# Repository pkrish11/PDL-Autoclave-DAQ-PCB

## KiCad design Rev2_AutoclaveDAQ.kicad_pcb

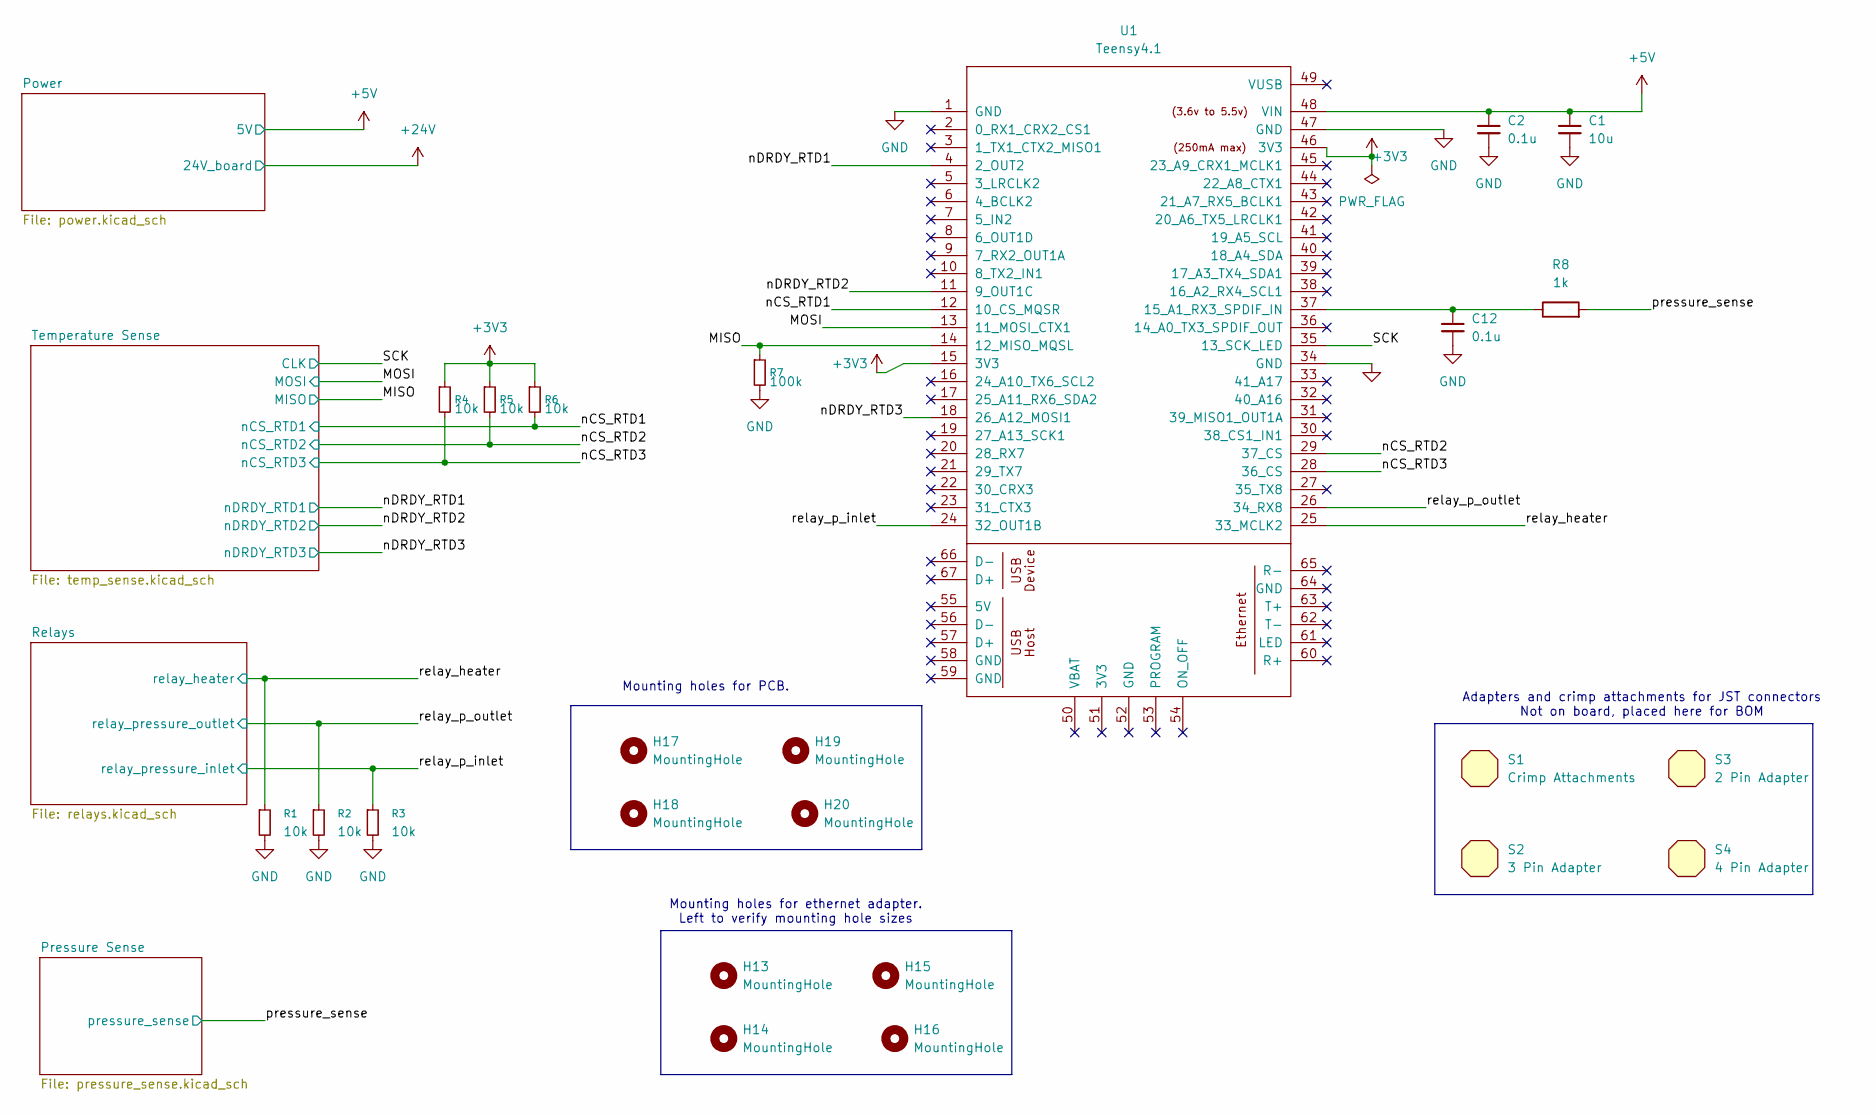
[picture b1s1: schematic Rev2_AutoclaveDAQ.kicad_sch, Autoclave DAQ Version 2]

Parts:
C1: 10u; C_0805_2012Metric; DigiKey_Part_Number 1276-2872-1-ND
C2, C12: 0.1u; C_0805_2012Metric; DigiKey_Part_Number 399-C0805C104K5RACTUCT-ND
H13, H14, H15, H16, H17, H18, H19, H20: MountingHole; MountingHole_3.2mm_M3
R1, R2, R3, R4, R5, R6: 10k; R_0805_2012Metric; DigiKey_Part_Number RMCF0805FT10K0CT-ND
R7: 100k; R_0805_2012Metric; DigiKey_Part_Number P100KDACT-ND
R8: 1k; R_0805_2012Metric; DigiKey_Part_Number 541-1.00KCCT-ND
S1: Crimp Attachments; DigiKey_Part_Number 455-1135TR-ND
S2: 3 Pin Adapter; DigiKey_Part_Number 455-2219-ND
S3: 2 Pin Adapter; DigiKey_Part_Number 455-2266-ND
S4: 4 Pin Adapter; DigiKey_Part_Number 455-2267-ND
U1: Teensy4.1; Teensy41

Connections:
+3V3: R4.1, R5.1, R6.1, U1.15 (3V3), U1.46 (3V3); also elsewhere on the board
+5V: C1.1, C2.1, U1.48 (VIN); also elsewhere on the board
/MISO: R7.1, U1.14 (12_MISO_MQSL); also elsewhere on the board
/MOSI: U1.13 (11_MOSI_CTX1); also elsewhere on the board
/SCK: U1.35 (13_SCK_LED); also elsewhere on the board
/nCS_RTD1: R6.2, U1.12 (10_CS_MQSR); also elsewhere on the board
/nCS_RTD2: R5.2, U1.29 (37_CS); also elsewhere on the board
/nCS_RTD3: R4.2, U1.28 (36_CS); also elsewhere on the board
/nDRDY_RTD1: U1.4 (2_OUT2); also elsewhere on the board
/nDRDY_RTD2: U1.11 (9_OUT1C); also elsewhere on the board
/nDRDY_RTD3: U1.18 (26_A12_MOSI1); also elsewhere on the board
/pressure_sense: R8.2; also elsewhere on the board
/relay_heater: R1.1, U1.25 (33_MCLK2); also elsewhere on the board
/relay_p_inlet: R3.1, U1.24 (32_OUT1B); also elsewhere on the board
/relay_p_outlet: R2.1, U1.26 (34_RX8); also elsewhere on the board
GND: C1.2, C2.2, C12.2, R1.2, R2.2, R3.2, R7.2, U1.1 (GND), U1.34 (GND), U1.47 (GND); also elsewhere on the board
unnamed: C12.1, R8.1, U1.37 (15_A1_RX3_SPDIF_IN)

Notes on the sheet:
Adapters and crimp attachments for JST connectors Not on board, placed here for BOM
Mounting holes for ethernet adapter. Left to verify mounting hole sizes
Mounting holes for PCB.

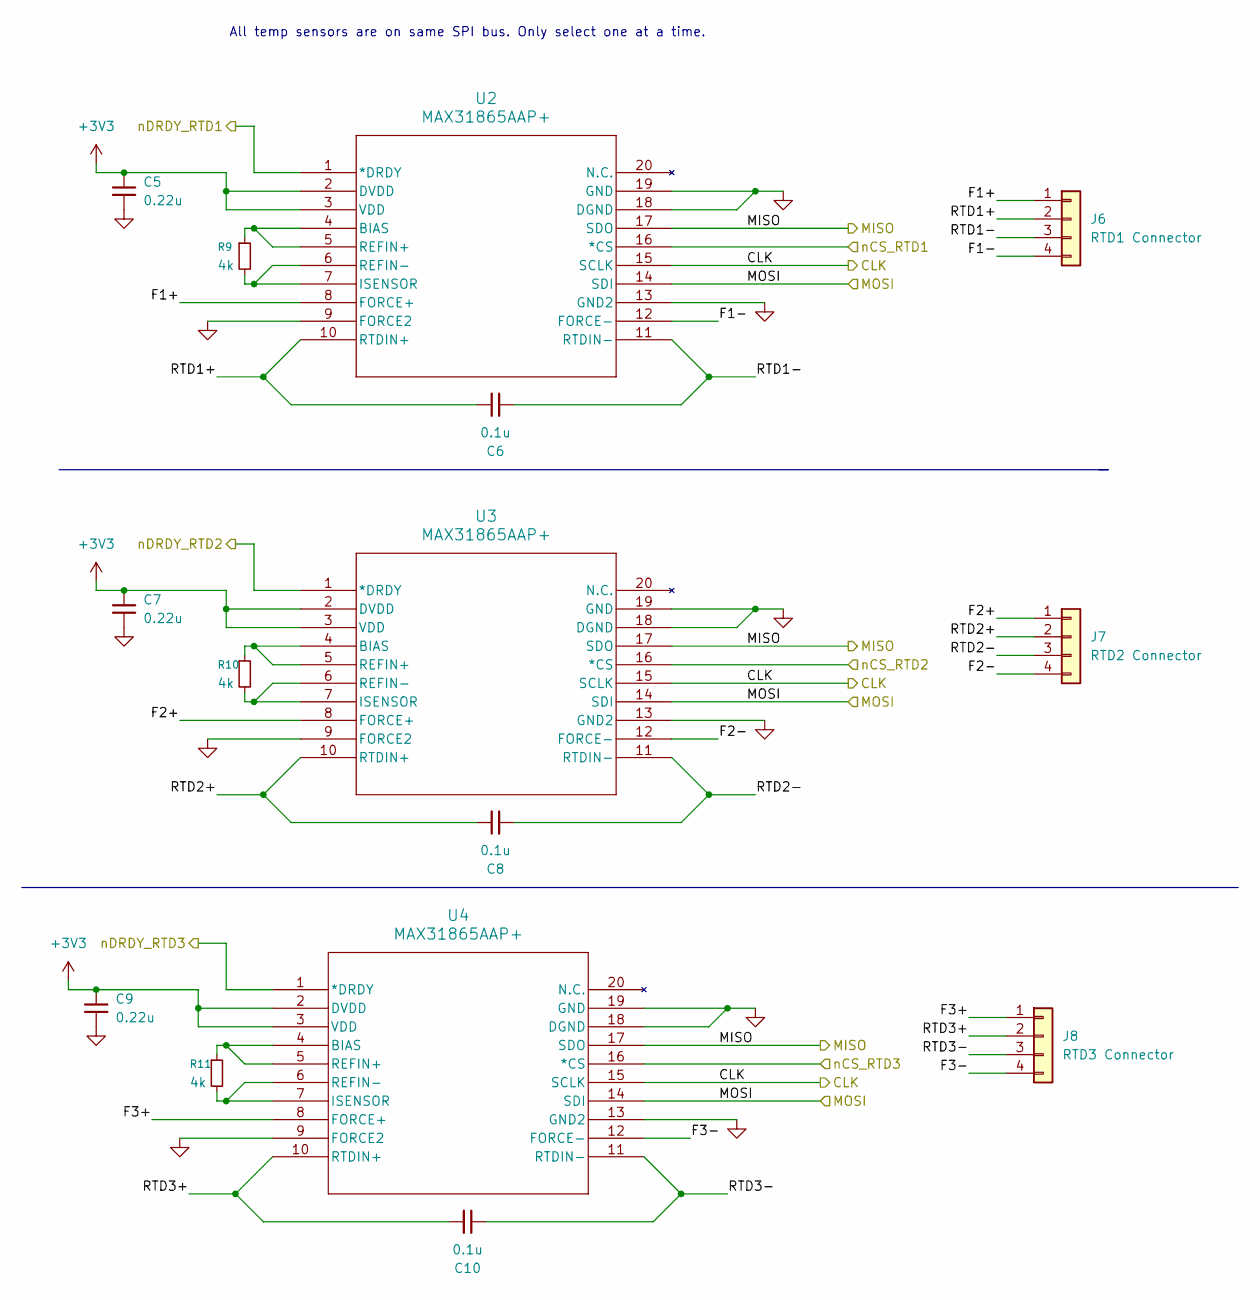
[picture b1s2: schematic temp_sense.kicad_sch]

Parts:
C5, C7, C9: 0.22u; C_0805_2012Metric; DigiKey_Part_Number 399-C0805C224K5RACTUCT-ND
C6, C8, C10: 0.1u; C_0805_2012Metric; DigiKey_Part_Number 399-C0805C104K5RACTUCT-ND
J6: RTD1 Connector; JST_XH_B4B-XH-A_1x04_P2.50mm_Vertical; DigiKey_Part_Number 455-B4B-XH-A-ND
J7: RTD2 Connector; JST_XH_B4B-XH-A_1x04_P2.50mm_Vertical; DigiKey_Part_Number 455-B4B-XH-A-ND
J8: RTD3 Connector; JST_XH_B4B-XH-A_1x04_P2.50mm_Vertical; DigiKey_Part_Number 455-B4B-XH-A-ND
R9, R10, R11: 4k; R_0805_2012Metric; DigiKey_Part_Number 738-RNCF0805BTY4K00CT-ND
U2, U3, U4: MAX31865AAP+; 21-0056C_20_MXM-M; DigiKey_Part_Number MAX31865AAP+

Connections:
+3V3: C5.1, C7.1, C9.1, U2.2 (DVDD), U2.3 (VDD), U3.2 (DVDD), U3.3 (VDD), U4.2 (DVDD), U4.3 (VDD); also elsewhere on the board
/MISO: U2.17 (SDO), U3.17 (SDO), U4.17 (SDO); also elsewhere on the board
/MOSI: U2.14 (SDI), U3.14 (SDI), U4.14 (SDI); also elsewhere on the board
/SCK: U2.15 (SCLK), U3.15 (SCLK), U4.15 (SCLK); also elsewhere on the board
/Temperature Sense/F1+: J6.1, U2.8 (FORCE+)
/Temperature Sense/F1-: J6.4, U2.12 (FORCE-)
/Temperature Sense/F2+: J7.1, U3.8 (FORCE+)
/Temperature Sense/F2-: J7.4, U3.12 (FORCE-)
/Temperature Sense/F3+: J8.1, U4.8 (FORCE+)
/Temperature Sense/F3-: J8.4, U4.12 (FORCE-)
/Temperature Sense/RTD1+: C6.1, J6.2, U2.10 (RTDIN+)
/Temperature Sense/RTD1-: C6.2, J6.3, U2.11 (RTDIN-)
/Temperature Sense/RTD2+: C8.1, J7.2, U3.10 (RTDIN+)
/Temperature Sense/RTD2-: C8.2, J7.3, U3.11 (RTDIN-)
/Temperature Sense/RTD3+: C10.1, J8.2, U4.10 (RTDIN+)
/Temperature Sense/RTD3-: C10.2, J8.3, U4.11 (RTDIN-)
/nCS_RTD1: U2.16 (*CS); also elsewhere on the board
/nCS_RTD2: U3.16 (*CS); also elsewhere on the board
/nCS_RTD3: U4.16 (*CS); also elsewhere on the board
/nDRDY_RTD1: U2.1 (*DRDY); also elsewhere on the board
/nDRDY_RTD2: U3.1 (*DRDY); also elsewhere on the board
/nDRDY_RTD3: U4.1 (*DRDY); also elsewhere on the board
GND: C5.2, C7.2, C9.2, U2.9 (FORCE2), U2.13 (GND2), U2.18 (DGND), U2.19 (GND), U3.9 (FORCE2), U3.13 (GND2), U3.18 (DGND), U3.19 (GND), U4.9 (FORCE2), U4.13 (GND2), U4.18 (DGND), U4.19 (GND); also elsewhere on the board
unnamed: R9.1, U2.4 (BIAS), U2.5 (REFIN+)
unnamed: R9.2, U2.6 (REFIN-), U2.7 (ISENSOR)
unnamed: R10.1, U3.4 (BIAS), U3.5 (REFIN+)
unnamed: R10.2, U3.6 (REFIN-), U3.7 (ISENSOR)
unnamed: R11.1, U4.4 (BIAS), U4.5 (REFIN+)
unnamed: R11.2, U4.6 (REFIN-), U4.7 (ISENSOR)

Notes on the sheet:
All temp sensors are on same SPI bus. Only select one at a time.

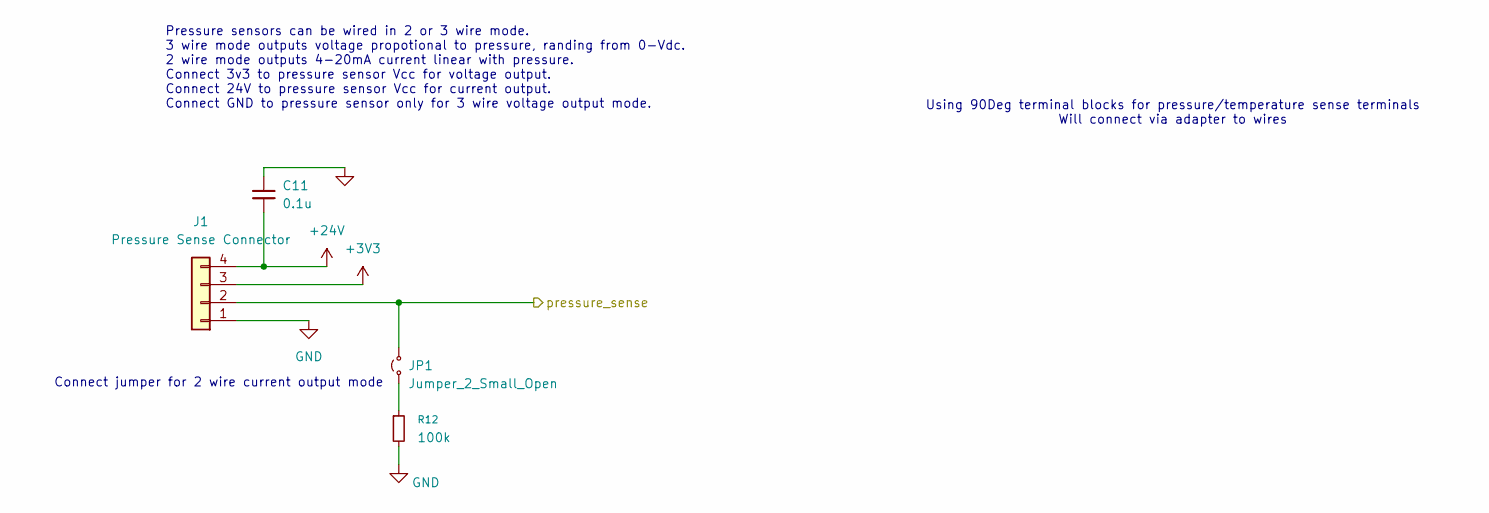
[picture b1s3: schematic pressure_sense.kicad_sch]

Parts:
C11: 0.1u; C_0805_2012Metric; DigiKey_Part_Number 399-C0805C104K5RACTUCT-ND
J1: Pressure Sense Connector; JST_XH_B4B-XH-A_1x04_P2.50mm_Vertical; DigiKey_Part_Number 455-B4B-XH-A-ND
JP1: Jumper_2_Small_Open; PinHeader_1x02_P2.54mm_Vertical
R12: 100k; R_0805_2012Metric; DigiKey_Part_Number P100KDACT-ND

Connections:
+3V3: J1.3; also elsewhere on the board
+24V: C11.2, J1.4; also elsewhere on the board
/pressure_sense: J1.2, JP1.2 (B); also elsewhere on the board
GND: C11.1, J1.1, R12.2; also elsewhere on the board
unnamed: JP1.1 (A), R12.1

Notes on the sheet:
Connect jumper for 2 wire current output mode
Using 90Deg terminal blocks for pressure/temperature sense terminals Will connect via adapter to wires
Pressure sensors can be wired in 2 or 3 wire mode. 3 wire mode outputs voltage propotional to pressure, randing from 0-Vdc. 2 wire mode outputs 4-20mA current linear with pressure. Connect 3v3 to pressure sensor Vcc for voltage output. Connect 24V to pressure sensor Vcc for current output. Connect 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

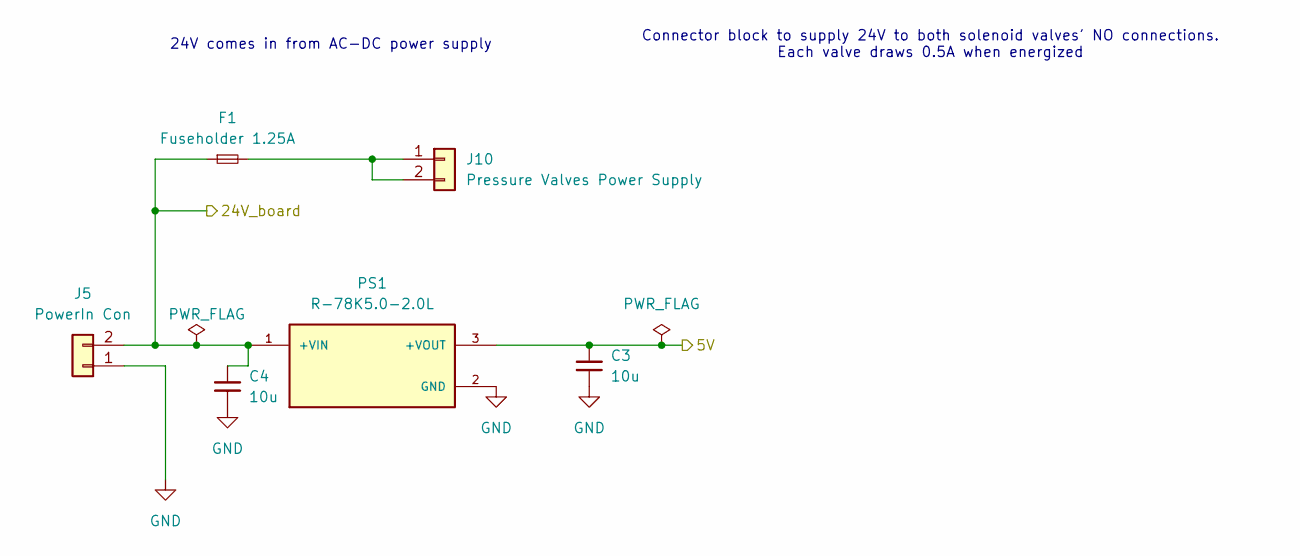
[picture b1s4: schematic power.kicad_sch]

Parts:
C3, C4: 10u; C_0805_2012Metric; DigiKey_Part_Number 1276-2872-1-ND
F1: Fuseholder 1.25A; Fuseholder_Cylinder-5x20mm_Wuerth_696103101002-SMD_Horizont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; DigiKey_Part_Number 732-11376-ND
J5: PowerIn Con; JST_XH_B2B-XH-A_1x02_P2.50mm_Vertical; DigiKey_Part_Number 455-B2B-XH-A-ND
J10: Pressure Valves Power Supply; JST_XH_B2B-XH-A_1x02_P2.50mm_Vertical; DigiKey_Part_Number 455-B2B-XH-A-ND
PS1: R-78K5.0-2.0L; CONV_R-78K5.0-2.0L; PARTREV 1; DigiKey_Part_Number 945-R-78K5.0-2.0L-ND

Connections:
+5V: C3.1, PS1.3 (+VOUT); also elsewhere on the board
+24V: C4.1, F1.1, J5.2, PS1.1 (+VIN); also elsewhere on the board
GND: C3.2, C4.2, J5.1, PS1.2 (GND); also elsewhere on the board
unnamed: F1.2, J10.1, J10.2

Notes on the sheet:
24V comes in from AC-DC power supply
Connector block to supply 24V to both solenoid valves' NO connections. Each valve draws 0.5A when energized

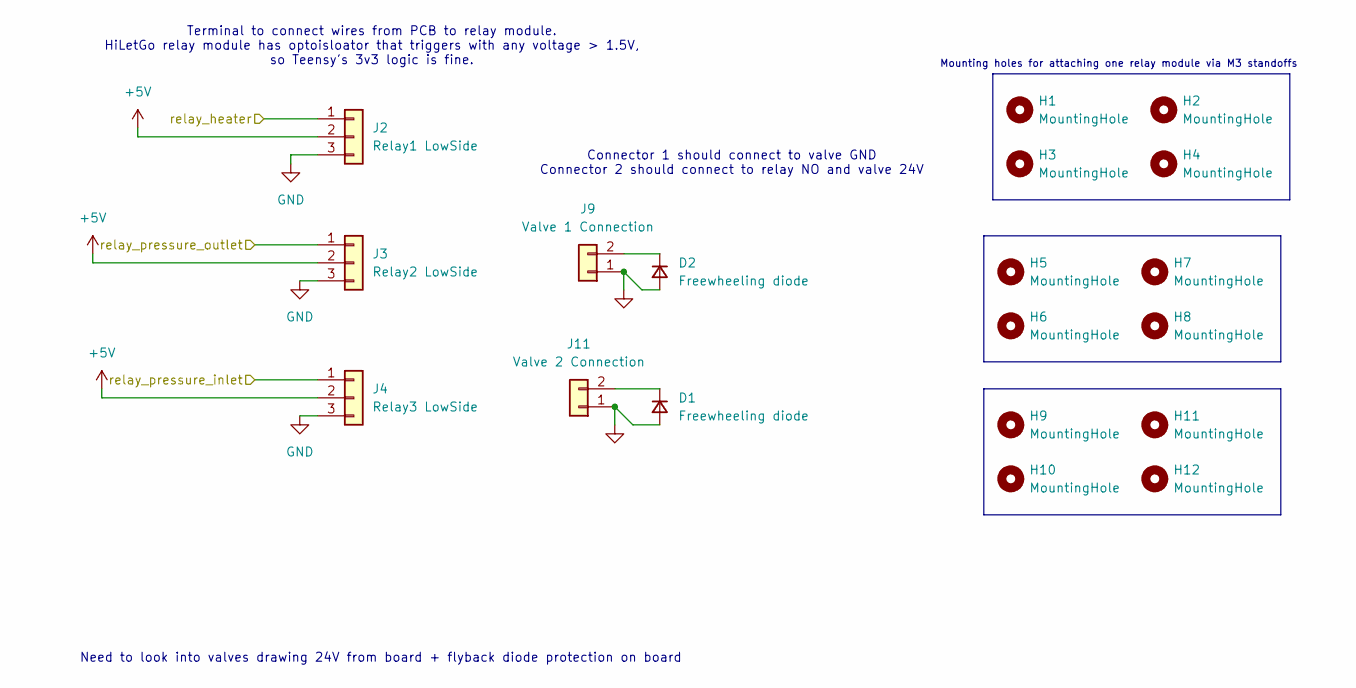
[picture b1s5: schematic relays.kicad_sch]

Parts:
D1, D2: Freewheeling diode; SMA_403AE_OSI-L
H1, H2, H3, H4, H5, H6, H7, H8, H9, H10, H11, H12: MountingHole; MountingHole_3.2mm_M3
J2: Relay1 LowSide; JST_XH_B3B-XH-A_1x03_P2.50mm_Vertical; DigiKey_Part_Number 455-2248-ND
J3: Relay2 LowSide; JST_XH_B3B-XH-A_1x03_P2.50mm_Vertical; DigiKey_Part_Number 455-2248-ND
J4: Relay3 LowSide; JST_XH_B3B-XH-A_1x03_P2.50mm_Vertical; DigiKey_Part_Number 455-2248-ND
J9: Valve 1 Connection; JST_XH_B2B-XH-A_1x02_P2.50mm_Vertical
J11: Valve 2 Connection; JST_XH_B2B-XH-A_1x02_P2.50mm_Vertical

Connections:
+5V: J2.2, J3.2, J4.2; also elsewhere on the board
/relay_heater: J2.1; also elsewhere on the board
/relay_p_inlet: J4.1; also elsewhere on the board
/relay_p_outlet: J3.1; also elsewhere on the board
GND: D1.2 (A), D2.2 (A), J2.3, J3.3, J4.3, J9.1, J11.1; also elsewhere on the board
unnamed: D1.1 (K), J11.2
unnamed: D2.1 (K), J9.2

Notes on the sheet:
Mounting holes for attaching one relay module via M3 standoffs
Terminal to connect wires from PCB to relay module. HiLetGo relay module has optoisloator that triggers with any voltage > 1.5V, so Teensy's 3v3 logic is fine.
Need to look into valves drawing 24V from board + flyback diode protection on board
Connector 1 should connect to valve GND Connector 2 should connect to relay NO and valve 24V

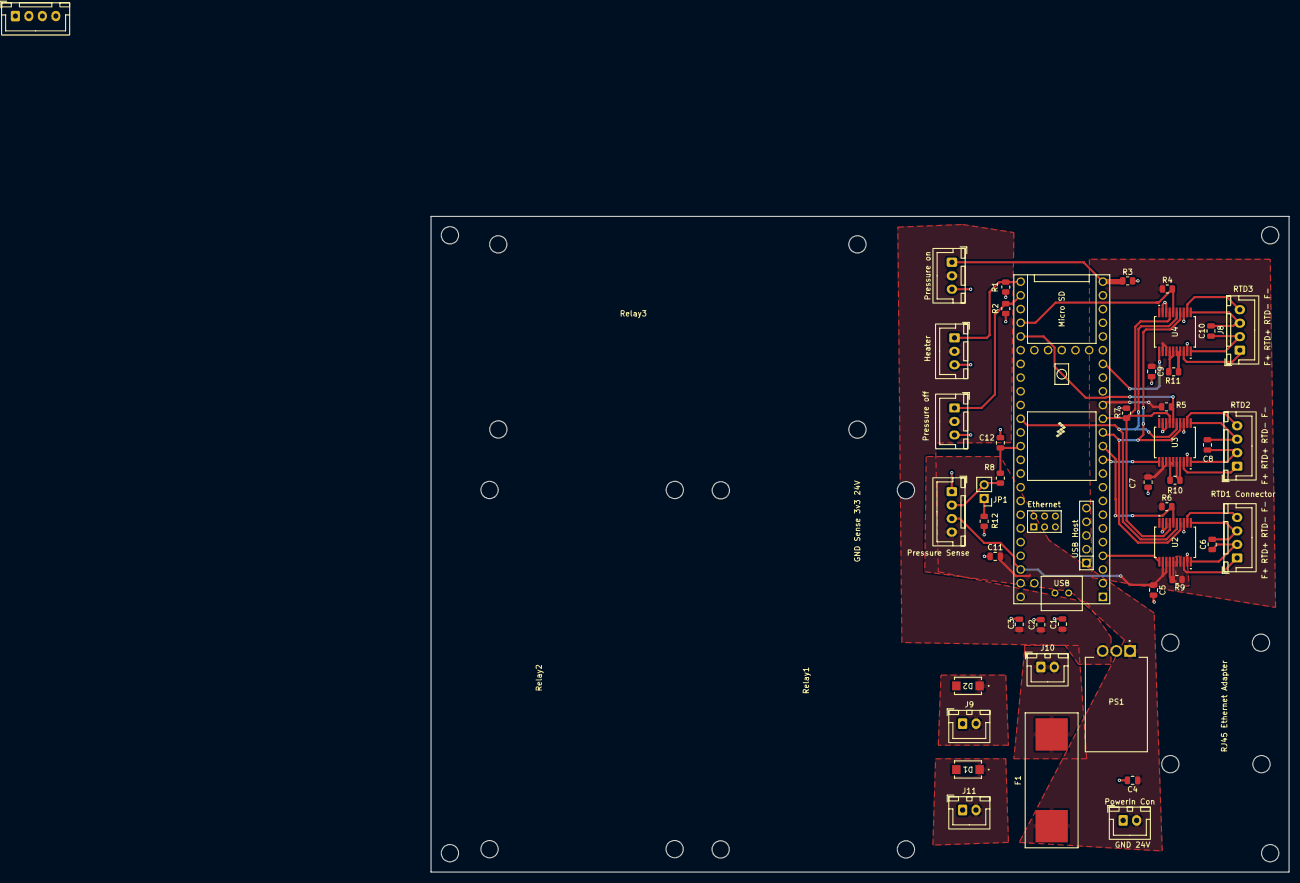
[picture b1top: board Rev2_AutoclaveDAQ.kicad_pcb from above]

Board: 2 copper layers, 159.0 x 121.5 mm, 65 parts (0 on the bottom side), 40 nets.

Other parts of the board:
GND Sense 3v3 24V: Pressure Sense; JST_XH_B4B-XH-A_1x04_P2.50mm_Vertical

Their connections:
+3V3: GND Sense 3v3 24V.3; also elsewhere on the board
+24V: GND Sense 3v3 24V.4; also elsewhere on the board
/pressure_sense: GND Sense 3v3 24V.2; also elsewhere on the board
GND: GND Sense 3v3 24V.1; also elsewhere on the board
